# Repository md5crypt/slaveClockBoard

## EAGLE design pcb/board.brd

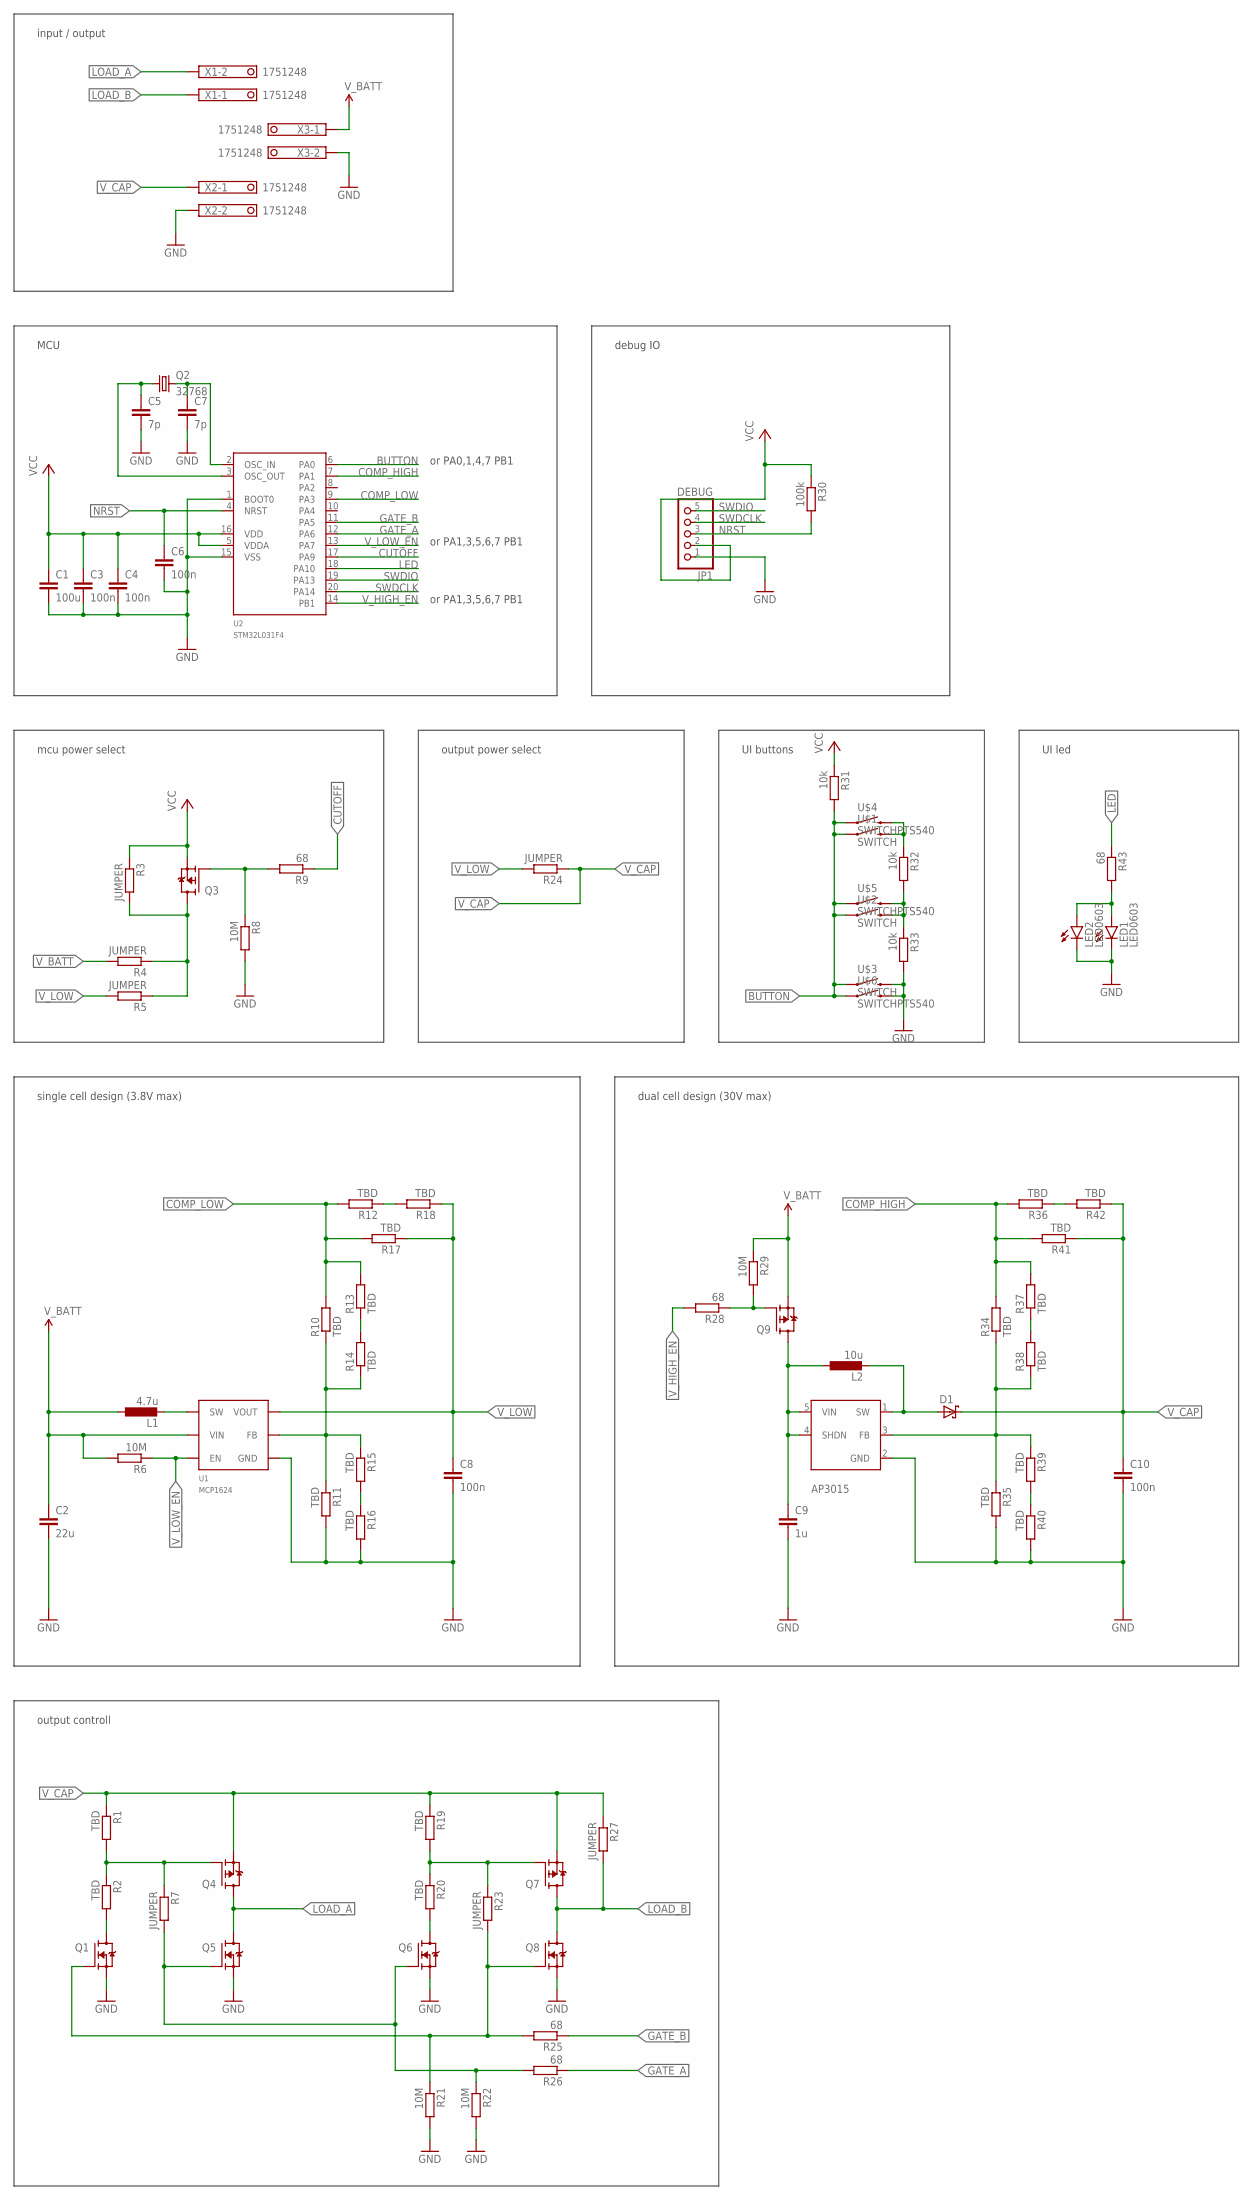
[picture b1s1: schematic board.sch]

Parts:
C1: 100u; 1206-SMALL
C2: 22u; 0805-SMALL
C3, C4, C6, C8, C10: 100n; 0603-SMALL
C5, C7: 7p; 0603-SMALL
C9: 1u; 0805-SMALL
D1: SCHOTTKY; DO-214
JP1: DEBUG; 1X05-S
L1: 4.7u; SRN2510F
L2: 10u; 74404043100A
LED1, LED2: LED0603; 0603-SMALL
Q1, Q5, Q6, Q8: NFETGENERIC; SOT23
Q2: 32768; ABS07
Q3, Q4, Q7, Q9: PFETIRLML6401; SOT23
R1, R2, R10, R11, R12, R13, R14, R15, R16, R17, R18, R19, R20, R34, R35, R36, R37, R38, R39, R40, R41, R42: TBD; 0603-SMALL
R3, R4, R5, R7, R23, R24, R27: JUMPER; 0603-SMALL
R6, R8, R21, R22, R29: 10M; 0603-SMALL
R9, R25, R26, R28, R43: 68; 0603-SMALL
R30: 100k; 0603-SMALL
R31, R32, R33: 10k; 0603-SMALL
U1: MCP1624; SOT23-6
U2: STM32L031F4; TSSOP20
U3: AP3015; SOT23-5
U$1, U$2, U$3: SWITCH; TACT-4.6X2.8
U$4, U$5, U$6: SWITCHPTS540; PTS540
X1, X2, X3: 1751248

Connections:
BUTTON: R31.2, U2.6 (PA0), U$1.P$1 (1), U$1.P$2 (1), U$2.P$1 (1), U$2.P$2 (1), U$3.P$1 (1), U$3.P$2 (1), U$4.1, U$4.2 (1), U$5.1, U$5.2 (1), U$6.1, U$6.2 (1)
COMP_HIGH: R34.2, R36.2, R37.2, R41.2, U2.7 (PA1)
COMP_LOW: R10.2, R12.2, R13.2, R17.2, U2.9 (PA3)
CUTOFF: R9.1, U2.17 (PA9)
GATE_A: R26.1, U2.12 (PA6)
GATE_B: R25.1, U2.11 (PA5)
GND: C1.2, C2.2, C3.2, C4.2, C5.2, C6.2, C7.2, C8.2, C9.2, C10.2, JP1.1, LED1.2 (C), LED2.2 (C), Q1.2 (S), Q5.2 (S), Q6.2 (S), Q8.2 (S), R8.2, R11.2, R16.2, R21.2, R22.2, R33.2, R35.2, R40.2, U1.2 (GND), U2.1 (BOOT0), U2.15 (VSS), U3.2 (GND), U$3.P$3 (2), U$3.P$4 (2), U$6.3 (2), U$6.4 (2), X2.2, X3.2
HBRIDGE_A: Q1.1 (G), Q8.1 (G), R21.1, R23.2, R25.2
HBRIDGE_B: Q5.1 (G), Q6.1 (G), R7.2, R22.1, R26.2
LED: R43.1, U2.18 (PA10)
LOAD_A: Q4.3 (D), Q5.3 (D), X1.2
LOAD_B: Q7.3 (D), Q8.3 (D), R27.2, X1.1
unnamed: C9.1, L2.P$1 (1), Q9.3 (D), U3.4 (SHDN), U3.5 (VIN)
unnamed: R32.1, U$1.P$3 (2), U$1.P$4 (2), U$4.3 (2), U$4.4 (2)
unnamed: L1.P$2 (2), U1.1 (SW)
unnamed: R32.2, R33.1, U$2.P$3 (2), U$2.P$4 (2), U$5.3 (2), U$5.4 (2)
unnamed: Q3.1 (G), R8.1, R9.2
unnamed: D1.P$1 (A), L2.P$2 (2), U3.1 (SW)
unnamed: R10.1, R11.1, R14.1, R15.1, U1.4 (FB)
unnamed: LED1.1 (A), LED2.1 (A), R43.2
unnamed: C7.1, Q2.P$2 (2), U2.2 (OSC_IN)
unnamed: R13.1, R14.2
unnamed: C5.1, Q2.P$1 (1), U2.3 (OSC_OUT)
unnamed: R15.2, R16.1
unnamed: R12.1, R18.2
unnamed: R39.2, R40.1
unnamed: R36.1, R42.2
unnamed: Q9.1 (G), R28.1, R29.2
unnamed: R37.1, R38.2
unnamed: R34.1, R35.1, R38.1, R39.1, U3.3 (FB)
unnamed: Q3.3 (D), R3.2, R4.1, R5.1
unnamed: Q4.1 (G), R1.2, R2.1, R7.1
unnamed: Q7.1 (G), R19.2, R20.1, R23.1
unnamed: Q1.3 (D), R2.2
unnamed: Q6.3 (D), R20.2
NRST: C6.1, JP1.3, R30.2, U2.4 (NRST)
SWDCLK: JP1.4, U2.20 (PA14)
SWDIO: JP1.5, U2.19 (PA13)
VCC: C1.1, C3.1, C4.1, JP1.2, Q3.2 (S), R3.1, R30.1, R31.1, U2.5 (VDDA), U2.16 (VDD)
V_BATT: C2.1, L1.P$1 (1), Q9.2 (S), R4.2, R6.2, R29.1, U1.6 (VIN), X3.1
V_CAP: C10.1, D1.P$2 (C), Q4.2 (S), Q7.2 (S), R1.1, R19.1, R24.1, R27.1, R41.1, R42.1, X2.1
V_HIGH_EN: R28.2, U2.14 (PB1)
V_LOW: C8.1, R5.2, R17.1, R18.1, R24.2, U1.5 (VOUT)
V_LOW_EN: R6.1, U1.3 (EN), U2.13 (PA7)

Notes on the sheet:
single cell design (3.8V max)
dual cell design (30V max)
mcu power select
output power select
output controll
or PA0,1,4,7 PB1
or PA1,3,5,6,7 PB1
UI buttons
UI led
debug IO
MCU
input / output

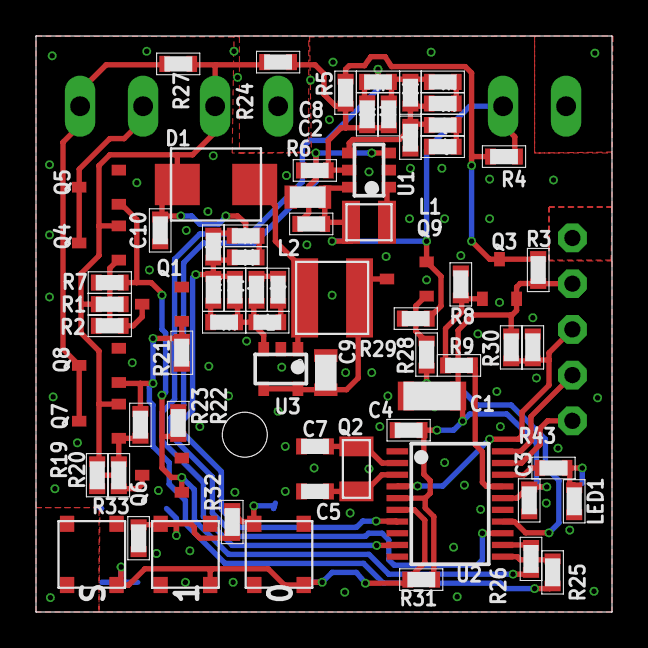
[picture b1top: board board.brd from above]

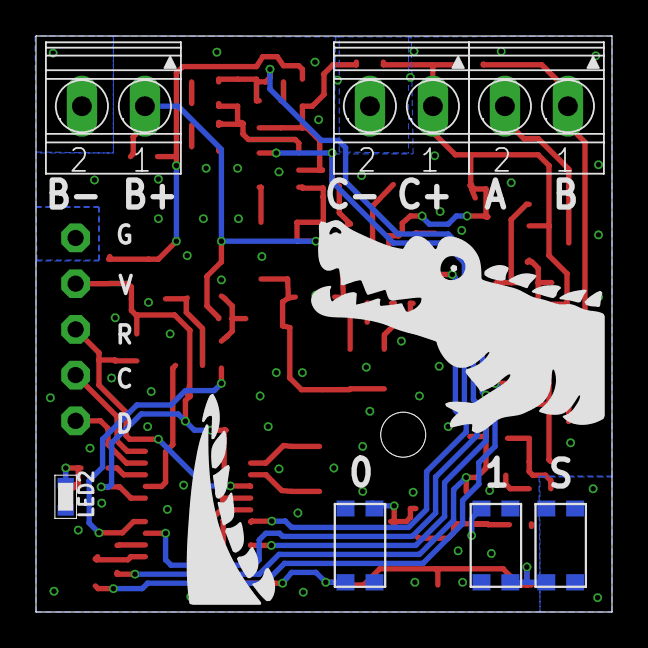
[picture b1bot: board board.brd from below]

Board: 2 copper layers, 32.0 x 32.0 mm, 80 parts (7 on the bottom side), 44 nets.

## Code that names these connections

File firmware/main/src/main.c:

#include <stdint.h>
#include <stdbool.h>
#include "stm32l0xx.h"
#include "gpio.h"

#define PIN_BUTTON     0
#define PIN_LED        10
#define PIN_GATE_A     6
#define PIN_GATE_B     5

#define PIN_BOOST_LOW  7
#define PIN_BOOST_HIGH 1 + 0x10
#define PIN_CUTOFF     9
#define PIN_DEBUG      14

#define PIN_COMP_HIGH  1
#define PIN_COMP_LOW   3

#define BOOT_ADDR    0x08000800
#define EEPROM_DATA  ((uint32_t*)0x08080000)
#define EEPROM_MAGIC 0xB16B00B5

#define INPUT_VOLTAGE_1_5   0
#define INPUT_VOLTAGE_3_0   1

#define OUTPUT_VOLTAGE_LOW  0
#define OUTPUT_VOLTAGE_HIGH 1

#define POLARITY_SINGLE 0
#define POLARITY_DOUBLE 1

typedef enum {
	STATE_INITIAL,
	STATE_IDLE,
	STATE_CHARGE,
	STATE_PULSE
} state_t;

typedef struct {
	uint32_t reload;
	uint32_t pulse;
	uint32_t charge;
	uint32_t prescaler;
	uint32_t fix_period;
	int32_t fix_offset;
	int32_t fix_sign;
	uint32_t fix_precision;
	uint32_t output_voltage;
	uint32_t input_voltage;
	uint32_t polarity;
} clock_config_t;

static clock_config_t config;
static uint32_t polarity;
static uint32_t comp_enabled;
static uint32_t button_offset;
static uint32_t charge_time;

static inline void mcu_reset() {
	RCC->APB1ENR |= RCC_APB1ENR_WWDGEN;
	WWDG->CR = WWDG_CR_WDGA;
}

static inline void stop(bool ulp, bool fwu){
	PWR->CR =
		PWR_CR_DSEEKOFF |         /* do not enable flash after wake-up */
		(fwu ? PWR_CR_FWU : 0) |  /* fast wake-up */
		(ulp ? PWR_CR_ULP : 0) |  /* disable vref in sleep */
		PWR_CR_LPSDSR |           /* enable low-power sleep */
		PWR_CR_VOS_1V5 |
		PWR_CR_CWUF;              /* clear wake-up flag */
	__WFE();                      /* sleep */
}

static void comp1_start() {
	// enable SYSCFG clock
	RCC->APB2ENR |= RCC_APB2ENR_SYSCFGEN;
	// enable COMP1
	if (config.output_voltage == OUTPUT_VOLTAGE_HIGH) {
		COMP1->CSR = COMP_CSR_COMP1EN;
	} else {
		COMP1->CSR = COMP_CSR_COMP1EN | COMP_CSR_COMP1WM;
	}
	// unmask COMP1 event
	EXTI->EMR |= EXTI_EMR_EM21;
	while (!(SYSCFG->CFGR3 & SYSCFG_CFGR3_VREFINT_RDYF)) {
		// wait
	}
	// clear COMP1 pending event flag
	EXTI->PR = EXTI_PR_PIF21;
	if (COMP1->CSR & COMP_CSR_COMP1VALUE) {
		EXTI->SWIER = EXTI_SWIER_SWI21;
	}
	comp_enabled = true;
}

static void comp1_stop() {
	// disable COMP1
	COMP1->CSR = 0;
	// disable SYSCFG clock
	RCC->APB2ENR &= ~RCC_APB2ENR_SYSCFGEN;
	// mask COMP1 event
	EXTI->EMR &= ~EXTI_EMR_EM21;
	comp_enabled = false;
}

static int32_t oscillator_calibration() {
	static uint32_t fix_cnt = 0;
	int32_t shift = config.fix_offset;
	if (config.fix_period > 0) {
		fix_cnt += config.fix_precision;
		if (fix_cnt >= config.fix_period) {
			fix_cnt -= config.fix_period;
			shift += config.fix_sign;
		}
	}
	return shift;
}

static void set_output() {
	if (config.polarity == POLARITY_SINGLE) {
		gpio_set(PIN_GATE_A);
	} else {
		if (polarity) {
			gpio_set(PIN_GATE_A);
		} else {
			gpio_set(PIN_GATE_B);
		}
		polarity ^= 1;
	}
}

static state_t next_state_single_cell(state_t state) {
	switch(state) {
		default:
		case STATE_INITIAL:
			LPTIM1->ARR = 1;
			return STATE_IDLE;
		case STATE_IDLE:
			gpio_clear(PIN_GATE_A);
			gpio_clear(PIN_GATE_B);
			gpio_set(PIN_BOOST_LOW);
			comp1_start();
			LPTIM1->ARR = config.reload - (config.pulse + config.charge + button_offset + 1) + oscillator_calibration();
			button_offset = 0;
			return STATE_CHARGE;
		case STATE_CHARGE:
			if (config.charge > 0) {
				gpio_set(PIN_BOOST_LOW);
				LPTIM1->ARR = config.charge - 1;
				return STATE_PULSE;
			}
			/* no break */
		case STATE_PULSE:
			gpio_set(PIN_CUTOFF);
			gpio_clear(PIN_BOOST_LOW);
			set_output();
			LPTIM1->ARR = config.pulse - 1;
			return STATE_IDLE;
	}
}

static state_t next_state_dual_cell(state_t state) {
	switch(state) {
		default:
		case STATE_INITIAL:
			LPTIM1->ARR = 1;
			return STATE_CHARGE;
		case STATE_IDLE:
			gpio_clear(PIN_GATE_A);
			gpio_clear(PIN_GATE_B);
			LPTIM1->ARR = config.reload - (config.pulse + config.charge + button_offset + charge_time + 1) + oscillator_calibration();
			button_offset = 0;
			return STATE_CHARGE;
		case STATE_CHARGE:
			comp1_start();
			gpio_set(PIN_CUTOFF);
			gpio_clear(PIN_BOOST_HIGH);
			LPTIM1->ARR = 0xFFFF;
			return STATE_PULSE;
		case STATE_PULSE:
			if (comp_enabled) {
				comp1_stop();
			}
			gpio_set(PIN_BOOST_HIGH);
			gpio_clear(PIN_CUTOFF);
			set_output();
			LPTIM1->ARR = config.pulse - 1;
			return STATE_IDLE;
	}
}

static state_t next_state(state_t state) {
	if (config.input_voltage == INPUT_VOLTAGE_1_5) {
		return next_state_single_cell(state);
	} else {
		return next_state_dual_cell(state);
	}
}

__attribute__((noreturn)) int main(){
	// enable SYSCFG clock
	RCC->APB2ENR |= RCC_APB2ENR_SYSCFGEN;
	// mount SRAM to boot sector
	SYSCFG->CFGR1 |= SYSCFG_CFGR1_MEM_MODE_SRAM;
	// disable SYSCFG clock
	RCC->APB2ENR &= ~RCC_APB2ENR_SYSCFGEN;

	// enable GPIO clock
	RCC->IOPENR |= RCC_IOPENR_GPIOAEN | RCC_IOPENR_GPIOBEN;

	// put all GPIO to analog mode
	GPIOA->MODER = 0xFFFFFFFF;

	// copy configuration from EEPROM
	if (EEPROM_DATA[0] == EEPROM_MAGIC) {
		for (uint32_t i = 0; i < sizeof(clock_config_t) / 4; i += 1) {
			((uint32_t*)&config)[i] = EEPROM_DATA[i + 1];
		}
	} else {
		// defaults
		config.reload = 30720;
		config.pulse = 50;
		config.prescaler = 6;
	}

	// set DC/DC converter enable
	if (config.output_voltage == OUTPUT_VOLTAGE_HIGH) {
		gpio_set(PIN_BOOST_HIGH);
		gpio_set_mode(PIN_BOOST_HIGH, GPIO_MODE_Output);
	} else {
		gpio_set(PIN_BOOST_LOW);
		gpio_set_mode(PIN_BOOST_LOW, GPIO_MODE_Output);
	}

	// set cuttoff
	gpio_set_mode(PIN_CUTOFF, GPIO_MODE_Output);

	// set gate output
	gpio_set_mode(PIN_GATE_A, GPIO_MODE_Output);
	if (config.polarity == POLARITY_DOUBLE) {
		gpio_set_mode(PIN_GATE_B, GPIO_MODE_Output);
	}

	// configure GPIO pin to check boot condition
	gpio_set_mode(PIN_BUTTON, GPIO_MODE_Input);

	// delay for a bit to wait for the pin to stabilize
	for (uint32_t i = 0; i < 50; i += 1) {
		__NOP();
	}

	// check pin status
	if (!gpio_read(PIN_BUTTON)) {
		// boot into configuration code
		SCB->VTOR = BOOT_ADDR;
		__set_MSP(((uint32_t*)BOOT_ADDR)[0]);
		((void (*)(void))((void*)((uint32_t*)BOOT_ADDR)[1]))();
	}

	// total flash power-down
	FLASH->PDKEYR = FLASH_PDKEYR_PDKEY1;
	FLASH->PDKEYR = FLASH_PDKEYR_PDKEY2;
	FLASH->ACR |= FLASH_ACR_RUN_PD;
	RCC->AHBENR &= ~RCC_AHBENR_MIFEN;

	// enable peripherals clocks
	RCC->APB1ENR |= RCC_APB1ENR_PWREN | RCC_APB1ENR_LPTIM1EN;
	RCC->APB1SMENR |= RCC_APB1SMENR_LPTIM1SMEN;

	// enable wake-on-event and deep sleep
	SCB->SCR |= SCB_SCR_SEVONPEND_Msk | SCB_SCR_SLEEPDEEP_Msk;

	// set clock speed and core voltage
	RCC->ICSCR = RCC_ICSCR_MSIRANGE_4M194;
	PWR->CR = PWR_CR_VOS_1V5;
	while(PWR->CSR&PWR_CSR_VOSF);

	// start the LSE clock
	PWR->CR |= PWR_CR_DBP;
	RCC->CSR |= RCC_CSR_LSEON | RCC_CSR_LSEDRV_0;
	PWR->CR ^= PWR_CR_DBP;
	while(!(RCC->CSR&RCC_CSR_LSERDY));

	// enable LPTIM1 event channel
	EXTI->EMR = (EXTI_EMR_EM0 << GPIO_PIN_NUM(PIN_BUTTON)) | EXTI_EMR_EM29;

	// falling edge sense on external int
	EXTI->FTSR = (EXTI_FTSR_FT0 << GPIO_PIN_NUM(PIN_BUTTON));

	// rising edge detection on COMP1
	EXTI->RTSR = EXTI_RTSR_RT21;

	// set LSE as LPTIM1 clock
	RCC->CCIPR = RCC_CCIPR_LPTIM1SEL_LSE;

	// configure LPTIM1
	LPTIM1->IER = LPTIM_IER_ARRMIE;
	LPTIM1->CFGR = (config.prescaler << LPTIM_CFGR_PRESC_Pos) | LPTIM_CFGR_TIMOUT; // reset timer on trigger
	LPTIM1->CR = LPTIM_CR_ENABLE;

	state_t state = next_state(STATE_INITIAL);

	// start timer
	while (!(LPTIM1->ISR&LPTIM_ISR_ARROK));
	LPTIM1->CR |= LPTIM_CR_CNTSTRT;

	// main loop
	while(1) {
		if (LPTIM1->ISR & LPTIM_ISR_ARRM) {
			while (!(LPTIM1->ISR & LPTIM_ISR_ARROK));
			LPTIM1->ICR = LPTIM_ICR_ARRMCF | LPTIM_ICR_ARROKCF;
			NVIC_ClearPendingIRQ(LPTIM1_IRQn);
			state = next_state(state);
		} else if (comp_enabled && (COMP1->CSR & COMP_CSR_COMP1VALUE)) {
			if (config.input_voltage == INPUT_VOLTAGE_1_5) {
				comp1_stop();
				EXTI->EMR |= (EXTI_EMR_EM0 << PIN_BUTTON);
				gpio_clear(PIN_BOOST_LOW);
				gpio_clear(PIN_CUTOFF);
			} else {
				while (!(LPTIM1->ISR & LPTIM_ISR_ARROK));
				LPTIM1->ICR = LPTIM_ICR_ARROKCF;
				comp1_stop();
				charge_time = LPTIM1->CNT;
				LPTIM1->ARR = charge_time + (config.charge - 1);
			}
		} else if ((state == STATE_CHARGE) && (!gpio_read(PIN_BUTTON))) {
			while (!(LPTIM1->ISR & LPTIM_ISR_ARROK));
			LPTIM1->ICR = LPTIM_ICR_ARROKCF;
			uint32_t cnt = 1000;
			while (cnt > 0) {
				if (gpio_read(PIN_BUTTON)) {
					cnt -= 1;
				} else {
					cnt += 1;
				}
				if (cnt > 100000) {
					mcu_reset();
				}
			}
			button_offset = (8000) >> config.prescaler;
			LPTIM1->ARR = LPTIM1->CNT + button_offset;
		}
		stop(!comp_enabled, true);
	}
}

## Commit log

2025-02-07 commit code

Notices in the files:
parts and their libraries:
SparkFun-Aesthetics: Licensing: Creative Commons ShareAlike 4.0 International - https://creativecommons.org/licenses/by-sa/4.0
